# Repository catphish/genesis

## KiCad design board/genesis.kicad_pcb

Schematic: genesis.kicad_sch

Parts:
C1, C2, C24, C39, C40, C42, C49, C51, C53, C59, C60, C98, C99, C100, C109, C110, C111, C112, C113, C114: 10u; C_0805_2012Metric; LCSC C15850
C3, C4, C5, C6, C7, C8, C9, C10, C11, C14, C15, C16, C17, C20, C23, C25, C26, C29, C30, C33, C34, C35, C38, C41, C43, C44, C46, C47, C54, C55, C56, C61, C62, C63, C64, C65, C66, C67, C68, C69, C70, C71, C72, C73, C74, C75, C76, C77, C78, C79, C80, C81, C82, C83, C84, C85, C86, C87, C88, C89, C90, C92, C93, C94, C95, C96, C97, C101, C102, C103, C104, C105, C106, C107, C108: 100n; C_0402_1005Metric; LCSC C307331
C12, C22, C37, C91: 4.7u; C_0805_2012Metric; LCSC C1779
C13, C18, C19, C27, C28, C31, C32, C45, C48, C57, C58: 2.2u; C_0603_1608Metric; LCSC C23630
C21: 33p; C_0402_1005Metric; LCSC C1562
C36: 22p; C_0402_1005Metric; LCSC C1555
C50, C52: 220p; C_0402_1005Metric; LCSC C1530
D1: LED_Dual_AAKK; LED_LiteOn_LTST-C295K_1.6x0.8mm; LCSC C364568
D2, D3: H3V3L10B; D_SOD-882; LCSC C20615781
D4: SMAJ10A; D_SMA; LCSC C134939
F1: nSMD100-16V; Fuse_1206_3216Metric; LCSC C70082
F2, F3: nSMD020-30V; Fuse_1206_3216Metric; LCSC C69680
H1, H2, H3, H4, H5, H6: MountingHole
J1: Conn_02x32_Row_Letter_First; CardEdge_MegaDrive_2x32_P2.54mm_Ears; LCSC C5242019
J2: HDMI_A_1.4; HDMI_A_Molex_208658-1001_Horizontal; LCSC C916313
J3: USB_C_Receptacle_USB2.0_14P; USB_C_Receptacle_Molex_217179-0001; LCSC C3197684
J4: DEBUG_POWER; PinHeader_1x02_P2.54mm_Vertical; LCSC C492401
J5, J6: DE9_Pins_MountingHoles; DSUB-9_Pins_Horizontal_P2.77x2.84mm_EdgePinOffset7.70mm_Hou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; LCSC C426221
JP1: 9V_SELECT; PinHeader_1x03_P2.54mm_Vertical; LCSC C2937625
L1, L2: 2.2u; L_Sunlord_MWSA0503S; LCSC C408408
L3: 1u; L_Sunlord_MWSA0503S; LCSC C408355
Q1, Q2, Q3, Q4, Q5: BSS138; SOT-23; LCSC C52895
Q6: AO3407A; SOT-23; LCSC C15155
R1, R2, R3, R4, R5, R6, R7, R8, R9, R10, R11, R12, R13, R14, R15, R16, R17, R18, R19, R20, R21, R22, R23, R24, R25, R26, R27, R28, R29, R30, R31, R32, R33, R34, R35, R36, R37, R38, R39, R40, R41, R42, R43, R44, R45, R46, R47, R48, R68, R85, R89, R148: 47k; R_0402_1005Metric; LCSC C25792
R49: 1k; R_0402_1005Metric; LCSC C11702
R50, R51, R52, R53, R54, R55: 22; R_0402_1005Metric; LCSC C25092
R56, R57, R58, R59, R60, R61, R62, R63, R64, R65: 270; R_0402_1005Metric; LCSC C25099
R66: 100k; R_0402_1005Metric; LCSC C25741
R67: 150k; R_0402_1005Metric; LCSC C25755
R69: 33k; R_0402_1005Metric; LCSC C25779
R70, R74, R76, R77, R79, R80, R82, R84, R86, R87, R88, R90, R96, R97, R98, R99, R100, R101, R102, R110, R111, R112, R113, R114, R115, R116, R117, R118, R119, R120, R121, R122, R123, R131, R132, R133, R134, R135, R136, R137, R138, R139, R140, R141, R142, R143, R144, R145, R147, R149: 10k; R_0402_1005Metric; LCSC C25744
R71: 53.6k; R_0402_1005Metric; LCSC C53398
R72: 220k; R_0402_1005Metric; LCSC C25767
R73: 8.45k; R_0402_1005Metric; LCSC C270579
R75: 30k; R_0402_1005Metric; LCSC C25776
R78, R81, R83, R91, R92, R93, R94, R95: 4.7k; R_0402_1005Metric; LCSC C25900
R103, R104, R105, R106, R107, R108, R109, R124, R125, R126, R127, R128, R129, R130: 220; R_0805_2012Metric; LCSC C17557
R146: 2.2k; R_0402_1005Metric; LCSC C25879
SW1: SW_RESET; SW_ALPS_SPPH4_Vertical; LCSC C202363
SW2: STM32_RESET; SW_SPST_B3U-1000P; LCSC C231329
SW3: STM32_DFU; SW_SPST_B3U-1000P; LCSC C231329
SW4: SW_POWER; SW_ALPS_SPPH4_Vertical; LCSC C370973
U1, U2, U3, U4, U5, U6, U7, U8, U9, U10, U11, U12, U13, U14, U15, U16, U17, U18, U19, U20, U21, U22, U23, U24, U25, U26, U27, U28, U29, U30, U31, U32, U33, U34, U35, U36, U37, U38, U39, U40, U41, U42, U43, U44, U45, U46, U47, U48, U49, U50, U51, U52, U53, U54, U55, U56, U57, U58, U59, U60, U61, U62, U63, U64, U65, U66, U67, U76, U77, U78, U79: TPD1E05U06DPY; Texas_DPY0002A_0.6x1mm_P0.65mm; LCSC C436349
U68: LFE5U-25F-6BG256C; BGA-256_14.0x14.0mm_Layout16x16_P0.8mm_Ball0.45mm_Pad0.32mm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; LCSC C1550762
U69: W25Q32JVZPIQ; WSON-8-1EP_6x5mm_P1.27mm_EP3.4x4.3mm; LCSC C571260
U70: LP5907MFX-2.5; SOT-23-5; LCSC C165132
U71, U72, U83: SN74ALVC164245DGG; TSSOP-48_6.1x12.5mm_P0.5mm; LCSC C7128
U73: IS61WV25616BLL; TSOP-II-44_10.16x18.41mm_P0.8mm; LCSC C53825
U74, U80, U81: TPS563257DRLR; SOT-563; LCSC C20539656
U75: STM32G431CBTx; LQFP-48_7x7mm_P0.5mm; LCSC C529355
U82: TPD12S016PWR; TSSOP-24_4.4x7.8mm_P0.65mm; LCSC C201665
U84: PCM1808PWR; TSSOP-14_4.4x5mm_P0.65mm; LCSC C55513
U85, U86, U87, U88, U89, U90, U91, U92, U93, U94, U95, U96, U97, U98: SN74LVC1T45DBV; SOT-23-6; LCSC C7843
Y1: 27MHz; Crystal_SMD_SeikoEpson_FA128-4Pin_2.0x1.6mm; LCSC C881727

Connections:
+1V1: C42.1, C92.1, C93.1, C94.1, C95.1, C96.1, C97.1, C98.1, C99.1, C100.1, L3.2, R73.1, U68.G6 (VCC[6]), U68.G7 (VCC[6]), U68.G9 (VCC[6]), U68.L8 (VCC[6]), U68.L9 (VCC[6]), U68.L10 (VCC[6])
+2V5: C19.1, C89.1, C90.1, C91.1, U68.G11 (VCCAUX[2]), U68.L7 (VCCAUX[2]), U70.5 (OUT)
+3V3: C3.1, C4.1, C5.1, C6.1, C7.1, C8.1, C9.1, C10.1, C11.1, C12.1, C13.1, C14.1, C15.1, C16.1, C17.1, C18.1, C21.1, C24.1, C33.1, C40.1, C41.1, C43.1, C44.1, C45.1, C46.1, C61.1, C62.1, C63.1, C64.1, C65.1, C66.1, C67.1, C68.1, C69.1, C70.1, C71.1, C72.1, C73.1, C74.1, C101.1, C102.1, C103.1, C104.1, C105.1, C106.1, C107.1, C108.1, C109.1, C110.1, C111.1, C112.1, C113.1, L1.2, Q1.1 (G), Q2.1 (G), Q3.1 (G), Q4.1 (G), Q5.1 (G), R49.2, R67.1, R78.2, R80.1, R81.2, R83.2, R86.2, R88.2, R90.2, R93.2, R94.2, R95.2, R139.1, R141.1, R143.1, R145.1, R147.1, R149.1, SW3.1, U68.F6 (VCCIO0[2]), U68.F7 (VCCIO0[2]), U68.F10 (VCCIO1[2]), U68.F11 (VCCIO1[2]), U68.H6 (VCCIO7[2]), U68.H7 (VCCIO7[2]), U68.H11 (VCCIO2[2]), U68.J6 (VCCIO6[2]), U68.J7 (VCCIO6[2]), U68.J11 (VCCIO2[2]), U68.K11 (VCCIO3[2]), U68.L6 (VCCIO8), U68.L11 (VCCIO3[2]), U68.P10 (CFG_1), U69.8 (VCC), U70.1 (IN), U70.3 (EN), U71.31 (V_{CC(A)}), U71.42 (V_{CC(A)}), U72.31 (V_{CC(A)}), U72.42 (V_{CC(A)}), U73.11 (VDD), U73.33 (VDD), U75.1 (VBAT), U75.20 (VREF+), U75.21 (VDDA), U75.24 (VDD), U75.36 (VDD), U75.48 (VDD), U81.1 (VIN), U81.5 (EN), U82.24 (VCCA), U83.31 (V_{CC(A)}), U83.42 (V_{CC(A)}), U84.4 (VDD), U85.1 (VCCA), U86.1 (VCCA), U87.1 (VCCA), U88.1 (VCCA), U89.1 (VCCA), U90.1 (VCCA), U91.1 (VCCA), U92.1 (VCCA), U93.1 (VCCA), U94.1 (VCCA), U95.1 (VCCA), U96.1 (VCCA), U97.1 (VCCA), U98.1 (VCCA), Y1.1 (EN), Y1.4 (Vdd)
+5V: C1.1, C2.1, C25.1, C26.1, C27.1, C28.1, C29.1, C30.1, C31.1, C32.1, C35.1, C36.1, C39.1, C47.1, C48.1, C55.1, C56.1, C57.1, C58.1, C75.1, C76.1, C77.1, C78.1, C79.1, C80.1, C81.1, C82.1, C83.1, C84.1, C85.1, C86.1, C87.1, C88.1, C114.1, F1.1, F2.1, F3.1, L2.2, R1.1, R2.1, R3.1, R4.1, R5.1, R6.1, R7.1, R8.1, R9.1, R10.1, R11.1, R12.1, R13.1, R14.1, R15.1, R16.1, R17.1, R18.1, R19.1, R20.1, R21.1, R22.1, R23.1, R24.1, R25.1, R26.1, R27.1, R28.1, R29.1, R30.1, R31.1, R32.1, R33.1, R34.1, R35.1, R36.1, R37.1, R38.1, R39.1, R40.1, R41.1, R42.1, R43.1, R44.1, R45.1, R46.1, R47.1, R48.1, R72.1, R96.1, R97.1, R98.1, R99.1, R100.1, R101.1, R102.1, R117.1, R118.1, R119.1, R120.1, R121.1, R122.1, R123.1, R138.1, R140.1, R142.1, R144.1, R146.1, U71.7 (V_{CC(B)}), U71.18 (V_{CC(B)}), U72.7 (V_{CC(B)}), U72.18 (V_{CC(B)}), U82.11 (VCC5V), U83.7 (V_{CC(B)}), U83.18 (V_{CC(B)}), U84.3 (VCC), U85.6 (VCCB), U86.6 (VCCB), U87.6 (VCCB), U88.6 (VCCB), U89.6 (VCCB), U90.6 (VCCB), U91.6 (VCCB), U92.6 (VCCB), U93.6 (VCCB), U94.6 (VCCB), U95.6 (VCCB), U96.6 (VCCB), U97.6 (VCCB), U98.6 (VCCB)
+9V: J4.2, JP1.1 (A)
/BOOT0: R70.2, SW3.2, U75.45 (PB8)
/STM32_RESET: C20.2, SW2.2, U75.7 (PG10)
BCK: U68.J13 (PR26C/+/RDQ29), U84.8 (BCK)
C1_P1_DATA: U68.B9 (PT47A/+/GR_PCLK1_0), U85.3 (A)
C1_P1_DIR: R110.1, U68.C9 (PT47B/-/GR_PCLK1_1), U85.5 (DIR)
C1_P1_PORT: J5.1, R103.1, U54.1 (I/O)
C1_P2_DATA: U68.D9 (PT49A/+), U86.3 (A)
C1_P2_DIR: R111.1, U68.E9 (PT49B/-), U86.5 (DIR)
C1_P2_PORT: J5.2, R104.1, U55.1 (I/O)
C1_P3_DATA: U68.A9 (PT51A/+), U87.3 (A)
C1_P3_DIR: R112.1, U68.A10 (PT51B/-), U87.5 (DIR)
C1_P3_PORT: J5.3, R105.1, U56.1 (I/O)
C1_P4_DATA: U68.B10 (PT53A/+), U88.3 (A)
C1_P4_DIR: R113.1, U68.C10 (PT53B/-), U88.5 (DIR)
C1_P4_PORT: J5.4, R106.1, U57.1 (I/O)
C1_P5_DATA: U68.D10 (PT56A/+), U89.3 (A)
C1_P5_DIR: R114.1, U68.E10 (PT56B/-), U89.5 (DIR)
C1_P5_PORT: J5.6, R107.1, U58.1 (I/O)
C1_P6_DATA: U68.B11 (PT58A/+), U90.3 (A)
C1_P6_DIR: R115.1, U68.C11 (PT58B/-), U90.5 (DIR)
C1_P6_PORT: J5.7, R108.1, U59.1 (I/O)
C1_P7_DATA: U68.D11 (PT69A/+), U91.3 (A)
C1_P7_DIR: R116.1, U68.E11 (PT69B/-), U91.5 (DIR)
C1_P7_PORT: J5.9, R109.1, U60.1 (I/O)
C2_P1_DATA: U68.A11 (PT71A/+), U92.3 (A)
C2_P1_DIR: R131.1, U68.A12 (PT71B/-), U92.5 (DIR)
C2_P1_PORT: J6.1, R124.1, U61.1 (I/O)
C2_P2_DATA: U68.B12 (PT74A/+), U93.3 (A)
C2_P2_DIR: R132.1, U68.C12 (PT74B/-), U93.5 (DIR)
C2_P2_PORT: J6.2, R125.1, U62.1 (I/O)
C2_P3_DATA: U68.D12 (PT76A/+), U94.3 (A)
C2_P3_DIR: R133.1, U68.E12 (PT76B/-), U94.5 (DIR)
C2_P3_PORT: J6.3, R126.1, U63.1 (I/O)
C2_P4_DATA: U68.B13 (PT78A/+), U95.3 (A)
C2_P4_DIR: R134.1, U68.C13 (PT78B/-), U95.5 (DIR)
C2_P4_PORT: J6.4, R127.1, U64.1 (I/O)
C2_P5_DATA: U68.D13 (PT80A/+), U96.3 (A)
C2_P5_DIR: R135.1, U68.E13 (PT80B/-), U96.5 (DIR)
C2_P5_PORT: J6.6, R128.1, U65.1 (I/O)
C2_P6_DATA: U68.A13 (PT83A/+), U97.3 (A)
C2_P6_DIR: R136.1, U68.A14 (PT83B/-), U97.5 (DIR)
C2_P6_PORT: J6.7, R129.1, U66.1 (I/O)
C2_P7_DATA: U68.B14 (PT85A/+/URC_GPLL1T_IN), U98.3 (A)
C2_P7_DIR: R137.1, U68.A15 (PT85B/-/URC_GPLL1C_IN), U98.5 (DIR)
C2_P7_PORT: J6.9, R130.1, U67.1 (I/O)
CART_ADDR_1: U68.L1 (PL35A/+/PCLKT6_1/HS/LDQ41), U83.47 (1A0)
CART_ADDR_2: U68.L2 (PL35B/-/PCLKC6_1/HS/LDQ41), U83.46 (1A1)
CART_ADDR_3: U68.M1 (PL35C/+/PCLKT6_0/LDQ41), U83.44 (1A2)
CART_ADDR_4: U68.M2 (PL35D/-/PCLKC6_0/LDQ41), U83.43 (1A3)
CART_ADDR_5: U68.K4 (PL38A/+/GR_PCLK6_0/HS/LDQ41), U83.41 (1A4)
CART_ADDR_6: U68.K5 (PL38B/-/HS/LDQ41), U83.40 (1A5)
CART_ADDR_7: U68.L4 (PL38C/+/GR_PCLK6_1/LDQ41), U83.38 (1A6)
CART_ADDR_8: U68.L5 (PL38D/-/LDQ41), U83.37 (1A7)
CART_ADDR_9: U68.N1 (PL41A/+/HS/LDQS41), U83.36 (2A0)
CART_ADDR_10: U68.P2 (PL41B/-/HS/LDQSN41), U83.35 (2A1)
CART_ADDR_11: U68.L3 (PL41C/+/LDQ41), U83.33 (2A2)
CART_ADDR_12: U68.M3 (PL41D/-/LDQ41), U83.32 (2A3)
CART_ADDR_13: U68.P1 (PL44A/+/HS/LDQ41), U83.30 (2A4)
CART_ADDR_14: U68.R1 (PL44B/-/VREF1_6/HS/LDQ41), U83.29 (2A5)
CART_ADDR_15: U68.M4 (PL44C/+/LDQ41), U83.27 (2A6)
CART_ADDR_16: U68.N3 (PL44D/-/LDQ41), U83.26 (2A7)
CART_ADDR_17: U68.N4 (PL59A/+/HS/LDQ65), U71.47 (1A0)
CART_ADDR_18: U68.P3 (PL59B/-/HS/LDQ65), U71.46 (1A1)
CART_ADDR_19: U68.R2 (PL59C/+/LDQ65), U71.44 (1A2)
CART_ADDR_20: U68.T2 (PL59D/-/LDQ65), U71.30 (2A4)
CART_ADDR_21: U68.P4 (PL62A/+/HS/LDQ65), U71.29 (2A5)
CART_ADDR_22: U68.R3 (PL62B/-/HS/LDQ65), U71.27 (2A6)
CART_ADDR_23: U68.R4 (PL62C/+/LDQ65), U71.26 (2A7)
CART_AS: U68.G3 (PL23C/+/VREF1_7/LDQ29), U71.35 (2A1)
CART_ASEL: U68.J5 (PL26D/-/LDQ29), U71.33 (2A2)
CART_CART: Q2.2 (S), R141.2, U68.J1 (PL32A/+/PCLKT7_1/HS/LDQ29)
CART_CAS0: U68.H4 (PL26B/-/HS/LDQ29), U71.43 (1A3)
CART_CAS2: U68.J4 (PL26C/+/LDQ29), U71.40 (1A5)
CART_CE0: U68.H3 (PL23D/-/LDQ29), U71.41 (1A4)
CART_DATA_0: U68.B1 (PL11A/+/ULC_GPLL0T_IN/HS/LDQ17), U72.47 (1A0)
CART_DATA_1: U68.B2 (PL11B/-/ULC_GPLL0C_IN/HS/LDQ17), U72.46 (1A1)
CART_DATA_2: U68.C3 (PL11C/+/LDQ17), U72.44 (1A2)
CART_DATA_3: U68.D3 (PL11D/-/LDQ17), U72.43 (1A3)
CART_DATA_4: U68.C1 (PL14A/+/HS/LDQ17), U72.41 (1A4)
CART_DATA_5: U68.C2 (PL14B/-/HS/LDQ17), U72.40 (1A5)
CART_DATA_6: U68.E3 (PL14C/+/LDQ17), U72.38 (1A6)
CART_DATA_7: U68.F3 (PL14D/-/LDQ17), U72.37 (1A7)
CART_DATA_8: U68.D1 (PL17A/+/HS/LDQS17), U72.36 (2A0)
CART_DATA_9: U68.E2 (PL17B/-/HS/LDQSN17), U72.35 (2A1)
CART_DATA_10: U68.F4 (PL17C/+/LDQ17), U72.33 (2A2)
CART_DATA_11: U68.F5 (PL17D/-/LDQ17), U72.32 (2A3)
CART_DATA_12: U68.G5 (PL20A/+/HS/LDQ17), U72.30 (2A4)
CART_DATA_13: U68.G4 (PL20B/-/HS/LDQ17), U72.29 (2A5)
CART_DATA_14: U68.F2 (PL20C/+/LDQ17), U72.27 (2A6)
CART_DATA_15: U68.E1 (PL20D/-/LDQ17), U72.26 (2A7)
CART_DATA_DIR: R87.1, U68.K2 (PL32D/-/PCLKC7_0/LDQ29), U72.1 (1DIR), U72.24 (2DIR)
CART_DATA_OE: R77.1, U68.K1 (PL32C/+/PCLKT7_0/LDQ29), U72.25 (2~OE), U72.48 (1~OE)
CART_DIR: R84.1, U68.K14 (PR29D/-/RDQ29), U71.1 (1DIR), U83.1 (1DIR), U83.24 (2DIR)
CART_DTACK: Q5.2 (S), R147.2, U68.K3 (PL29D/-/LDQ29)
CART_LWR: U68.H2 (PL29B/-/HS/LDQSN29), U71.37 (1A7)
CART_M3: Q1.2 (S), R139.2, U68.J2 (PL32B/-/PCLKC7_1/HS/LDQ29)
CART_MRES: Q4.2 (S), R145.2, U68.K16 (PR32C/+/PCLKT2_0/RDQ29)
CART_OE: R79.1, U68.J16 (PR32A/+/PCLKT2_1/HS/RDQ29), U71.25 (2~OE), U71.48 (1~OE), U83.25 (2~OE), U83.48 (1~OE)
CART_SLOT_ADDR_1: J1.a17, R17.2, U32.1 (I/O), U83.2 (1B0)
CART_SLOT_ADDR_2: J1.a15, R18.2, U30.1 (I/O), U83.3 (1B1)
CART_SLOT_ADDR_3: J1.a13, R19.2, U28.1 (I/O), U83.5 (1B2)
CART_SLOT_ADDR_4: J1.a11, R20.2, U27.1 (I/O), U83.6 (1B3)
CART_SLOT_ADDR_5: J1.a9, R21.2, U33.1 (I/O), U83.8 (1B4)
CART_SLOT_ADDR_6: J1.a7, R22.2, U23.1 (I/O), U83.9 (1B5)
CART_SLOT_ADDR_7: J1.a5, R23.2, U21.1 (I/O), U83.11 (1B6)
CART_SLOT_ADDR_8: J1.a3, R24.2, U19.1 (I/O), U83.12 (1B7)
CART_SLOT_ADDR_9: J1.b4, R25.2, U18.1 (I/O), U83.13 (2B0)
CART_SLOT_ADDR_10: J1.b5, R26.2, U6.1 (I/O), U83.14 (2B1)
CART_SLOT_ADDR_11: J1.a4, R27.2, U20.1 (I/O), U83.16 (2B2)
CART_SLOT_ADDR_12: J1.a6, R28.2, U22.1 (I/O), U83.17 (2B3)
CART_SLOT_ADDR_13: J1.a8, R29.2, U24.1 (I/O), U83.19 (2B4)
CART_SLOT_ADDR_14: J1.a10, R30.2, U25.1 (I/O), U83.20 (2B5)
CART_SLOT_ADDR_15: J1.a12, R31.2, U26.1 (I/O), U83.22 (2B6)
CART_SLOT_ADDR_16: J1.a14, R32.2, U29.1 (I/O), U83.23 (2B7)
CART_SLOT_ADDR_17: J1.a16, R33.2, U31.1 (I/O), U71.2 (1B0)
CART_SLOT_ADDR_18: J1.b6, R34.2, U17.1 (I/O), U71.3 (1B1)
CART_SLOT_ADDR_19: J1.b7, R35.2, U16.1 (I/O), U71.5 (1B2)
CART_SLOT_ADDR_20: J1.b8, R36.2, U53.1 (I/O), U71.19 (2B4)
CART_SLOT_ADDR_21: J1.b9, R37.2, U52.1 (I/O), U71.20 (2B5)
CART_SLOT_ADDR_22: J1.b10, R38.2, U51.1 (I/O), U71.22 (2B6)
CART_SLOT_ADDR_23: J1.b11, R39.2, U50.1 (I/O), U71.23 (2B7)
CART_SLOT_AS: J1.b18, R46.2, U2.1 (I/O), U71.14 (2B1)
CART_SLOT_ASEL: J1.b26, R47.2, U9.1 (I/O), U71.16 (2B2)
CART_SLOT_CART: J1.b32, Q2.3 (D), R140.2, U15.1 (I/O)
CART_SLOT_CAS0: J1.b16, R40.2, U7.1 (I/O), U71.6 (1B3)
CART_SLOT_CAS2: J1.b21, R42.2, U8.1 (I/O), U71.9 (1B5)
CART_SLOT_CE0: J1.b17, R41.2, U3.1 (I/O), U71.8 (1B4)
CART_SLOT_DATA_0: J1.a20, R1.2, U39.1 (I/O), U72.2 (1B0)
CART_SLOT_DATA_1: J1.a23, R2.2, U42.1 (I/O), U72.3 (1B1)
CART_SLOT_DATA_2: J1.a26, R3.2, U45.1 (I/O), U72.5 (1B2)
CART_SLOT_DATA_3: J1.a29, R4.2, U48.1 (I/O), U72.6 (1B3)
CART_SLOT_DATA_4: J1.a28, R5.2, U47.1 (I/O), U72.8 (1B4)
CART_SLOT_DATA_5: J1.a25, R6.2, U44.1 (I/O), U72.9 (1B5)
CART_SLOT_DATA_6: J1.a22, R7.2, U41.1 (I/O), U72.11 (1B6)
CART_SLOT_DATA_7: J1.a19, R8.2, U38.1 (I/O), U72.12 (1B7)
CART_SLOT_DATA_8: J1.a21, R9.2, U40.1 (I/O), U72.13 (2B0)
CART_SLOT_DATA_9: J1.a24, R10.2, U43.1 (I/O), U72.14 (2B1)
CART_SLOT_DATA_10: J1.a27, R11.2, U46.1 (I/O), U72.16 (2B2)
CART_SLOT_DATA_11: J1.a30, R12.2, U49.1 (I/O), U72.17 (2B3)
CART_SLOT_DATA_12: J1.b25, R13.2, U34.1 (I/O), U72.19 (2B4)
CART_SLOT_DATA_13: J1.b24, R14.2, U35.1 (I/O), U72.20 (2B5)
CART_SLOT_DATA_14: J1.b23, R15.2, U36.1 (I/O), U72.22 (2B6)
CART_SLOT_DATA_15: J1.b22, R16.2, U37.1 (I/O), U72.23 (2B7)
CART_SLOT_DTACK: J1.b20, Q5.3 (D), R146.2, U5.1 (I/O)
CART_SLOT_EDCLK: J1.b15
CART_SLOT_HSYNC: J1.b14
CART_SLOT_LWR: J1.b28, R44.2, U11.1 (I/O), U71.12 (1B7)
CART_SLOT_M3: J1.b30, Q1.3 (D), R138.2, U13.1 (I/O)
CART_SLOT_MRES: J1.b2, Q4.3 (D), R144.2, U1.1 (I/O)
CART_SLOT_SL1: C49.1, D2.2 (A2), J1.b1, R85.2
CART_SLOT_SR1: C51.1, D3.2 (A2), J1.b3, R89.2
CART_SLOT_TIME: J1.b31, R48.2, U14.1 (I/O), U71.17 (2B3)
CART_SLOT_UWR: J1.b29, R45.2, U12.1 (I/O), U71.13 (2B0)
CART_SLOT_VCLK: J1.b19, R43.2, U4.1 (I/O), U71.11 (1B6)
CART_SLOT_VRES: J1.b27, Q3.3 (D), R142.2, U10.1 (I/O)
CART_SLOT_VSYNC: J1.b13
CART_SLOT_YS: J1.b12
CART_TIME: U68.H5 (PL26A/+/HS/LDQ29), U71.32 (2A3)
CART_UWR: U68.G1 (PL29A/+/GR_PCLK7_1/HS/LDQS29), U71.36 (2A0)
CART_VA_HI_DIR: R82.1, U68.J15 (PR32B/-/PCLKC2_1/HS/RDQ29), U71.24 (2DIR)
CART_VCLK: U68.J3 (PL29C/+/GR_PCLK7_0/LDQ29), U71.38 (1A6)
CART_VRES: Q3.2 (S), R143.2, U68.K15 (PR32D/-/PCLKC2_0/RDQ29)
CC1: C50.1, J3.A5 (CC1), U75.31 (PA9), U75.43 (PB6), U78.1 (I/O)
CC2: C52.1, J3.B5 (CC2), U75.32 (PA10), U75.41 (PB4), U79.1 (I/O)
CLK_MASTER: U68.E8 (PT42A/+/PCLKT1_1), Y1.3 (OUT)
D+: J3.A6 (D+), J3.B6 (D+), U75.34 (PA12), U76.1 (I/O)
D-: J3.A7 (D-), J3.B7 (D-), U75.33 (PA11), U77.1 (I/O)
DONE: R81.1, U68.P9 (DONE), U75.10 (PA2)
DOUT: U68.H12 (PR26A/+/HS/RDQ29), U84.9 (DOUT)
FLASH_CLK: R49.1, R50.1, U69.6 (CLK)
FLASH_CS_N: R55.1, R86.1, U69.1 (~CS)
FLASH_D0: R54.1, U69.5 (DI/IO_{0})
FLASH_D1: R53.1, U69.2 (DO/IO_{1})
FLASH_D2: R52.1, R88.1, U69.3 (~WP/IO_{2})
FLASH_D3: R51.1, R90.1, U69.7 (~HOLD/~RESET/IO_{3})
GND: C1.2, C2.2, C3.2, C4.2, C5.2, C6.2, C7.2, C8.2, C9.2, C10.2, C11.2, C12.2, C13.2, C14.2, C15.2, C16.2, C17.2, C18.2, C19.2, C20.1, C22.2, C23.2, C24.2, C25.2, C26.2, C27.2, C28.2, C29.2, C30.2, C31.2, C32.2, C33.2, C34.2, C35.2, C37.2, C38.2, C39.2, C40.2, C41.2, C42.2, C43.2, C44.2, C45.2, C46.2, C47.2, C48.2, C50.2, C52.2, C53.2, C54.2, C55.2, C56.2, C57.2, C58.2, C59.1, C60.1, C61.2, C62.2, C63.2, C64.2, C65.2, C66.2, C67.2, C68.2, C69.2, C70.2, C71.2, C72.2, C73.2, C74.2, C75.2, C76.2, C77.2, C78.2, C79.2, C80.2, C81.2, C82.2, C83.2, C84.2, C85.2, C86.2, C87.2, C88.2, C89.2, C90.2, C91.2, C92.2, C93.2, C94.2, C95.2, C96.2, C97.2, C98.2, C99.2, C100.2, C101.2, C102.2, C103.2, C104.2, C105.2, C106.2, C107.2, C108.2, C109.2, C110.2, C111.2, C112.2, C113.2, C114.2, D1.3 (K1), D1.4 (K2), D2.1 (A1), D3.1 (A1), D4.2 (A2), J1.a1, J1.a18, J1.a32, J2.2 (D2S), J2.5 (D1S), J2.8 (D0S), J2.11 (CKS), J2.17 (GND), J2.SH, J3.A1 (GND), J3.A12 (GND), J3.B1 (GND), J3.B12 (GND), J3.SH (SHIELD), J4.1, J5.8, J5.SH (PAD), J6.8, J6.SH (PAD), R68.2, R69.2, R70.1, R74.2, R75.2, R76.2, R77.2, R79.2, R82.2, R84.2, R85.1, R87.2, R89.1, R91.2, R92.2, R110.2, R111.2, R112.2, R113.2, R114.2, R115.2, R116.2, R131.2, R132.2, R133.2, R134.2, R135.2, R136.2, R137.2, SW1.1, SW2.1, SW4.1 (A), U1.2 (GND), U2.2 (GND), U3.2 (GND), U4.2 (GND), U5.2 (GND), U6.2 (GND), U7.2 (GND), U8.2 (GND), U9.2 (GND), U10.2 (GND), U11.2 (GND), U12.2 (GND), U13.2 (GND), U14.2 (GND), U15.2 (GND), U16.2 (GND), U17.2 (GND), U18.2 (GND), U19.2 (GND), U20.2 (GND), U21.2 (GND), U22.2 (GND), U23.2 (GND), U24.2 (GND), U25.2 (GND), U26.2 (GND), U27.2 (GND), U28.2 (GND), U29.2 (GND), U30.2 (GND), U31.2 (GND), U32.2 (GND), U33.2 (GND), U34.2 (GND), U35.2 (GND), U36.2 (GND), U37.2 (GND), U38.2 (GND), U39.2 (GND), U40.2 (GND), U41.2 (GND), U42.2 (GND), U43.2 (GND), U44.2 (GND), U45.2 (GND), U46.2 (GND), U47.2 (GND), U48.2 (GND), U49.2 (GND), U50.2 (GND), U51.2 (GND), U52.2 (GND), U53.2 (GND), U54.2 (GND), U55.2 (GND), U56.2 (GND), U57.2 (GND), U58.2 (GND), U59.2 (GND), U60.2 (GND), U61.2 (GND), U62.2 (GND), U63.2 (GND), U64.2 (GND), U65.2 (GND), U66.2 (GND), U67.2 (GND), U68.A1 (GND[27]), U68.A16 (GND[27]), U68.D2 (GND[27]), U68.D15 (GND[27]), U68.F8 (GND[27]), U68.F9 (GND[27]), U68.G8 (GND[27]), U68.G10 (GND[27]), U68.H1 (GND[27]), U68.H8 (GND[27]), U68.H9 (GND[27]), U68.H10 (GND[27]), U68.H16 (GND[27]), U68.J8 (GND[27]), U68.J9 (GND[27]), U68.J10 (GND[27]), U68.K6 (GND[27]), U68.K7 (GND[27]), U68.K8 (GND[27]), U68.K9 (GND[27]), U68.K10 (GND[27]), U68.N2 (GND[27]), U68.N10 (CFG_0), U68.N15 (GND[27]), U68.R10 (CFG_2), U68.T1 (GND[27]), U68.T5 (GND[27]), U68.T12 (GND[27]), U68.T16 (GND[27]), U69.4 (GND), U69.9 (EP), U70.2 (GND), U71.4 (GND), U71.10 (GND), U71.15 (GND), U71.21 (GND), U71.28 (GND), U71.34 (GND), U71.39 (GND), U71.45 (GND), U72.4 (GND), U72.10 (GND), U72.15 (GND), U72.21 (GND), U72.28 (GND), U72.34 (GND), U72.39 (GND), U72.45 (GND), U73.12 (GND), U73.34 (GND), U74.3 (GND), U75.19 (VSSA), U75.23 (VSS), U75.35 (VSS), U75.47 (VSS), U76.2 (GND), U77.2 (GND), U78.2 (GND), U79.2 (GND), U80.3 (GND), U81.3 (GND), U82.6 (GND), U82.14 (GND), U82.19 (GND), U83.4 (GND), U83.10 (GND), U83.15 (GND), U83.21 (GND), U83.28 (GND), U83.34 (GND), U83.39 (GND), U83.45 (GND), U84.2 (AGND), U84.5 (DGND), U84.10 (MD0), U84.11 (MD1), U84.12 (FMT), U85.2 (GND), U86.2 (GND), U87.2 (GND), U88.2 (GND), U89.2 (GND), U90.2 (GND), U91.2 (GND), U92.2 (GND), U93.2 (GND), U94.2 (GND), U95.2 (GND), U96.2 (GND), U97.2 (GND), U98.2 (GND), Y1.2 (GND)
HDMI_5V: C34.1, J2.18 (+5V), U82.13 (5V_OUT)
HDMI_CEC: U68.D5 (PT13B/-), U82.1 (CEC_A)
HDMI_CLK+: R64.1, U68.C4 (PT11A/+), U82.16 (CLK+)
HDMI_CLK-: R65.1, U68.B4 (PT11B/-), U82.15 (CLK-)
HDMI_CT_HPD: U68.A6 (PT18B/-), U82.12 (CT_HPD)
HDMI_D0+: R62.1, U68.A2 (PT4A/+/ULC_GPLL1T_IN), U82.18 (D0+)
HDMI_D0-: R63.1, U68.B3 (PT4B/-/ULC_GPLL1C_IN), U82.17 (D0-)
HDMI_D1+: R59.1, U68.A3 (PT6A/+), U82.21 (D1+)
HDMI_D1-: R60.1, U68.A4 (PT6B/-), U82.20 (D1-)
HDMI_D2+: R56.1, U68.E4 (PT9A/+), U82.23 (D2+)
HDMI_D2-: R57.1, U68.D4 (PT9B/-), U82.22 (D2-)
HDMI_HPD: U68.A5 (PT18A/+), U82.4 (HPD_A)
HDMI_LS_OE: U68.E6 (PT20A/+), U82.5 (LS_OE)
HDMI_PORT_CEC: J2.13 (CEC), U82.7 (CEC_B)
HDMI_PORT_HPD: J2.19 (HPD/HEAC-), U82.10 (HPD_B)
HDMI_PORT_SCL: J2.15 (SCL), U82.8 (SCL_B)
HDMI_PORT_SDA: J2.16 (SDA), U82.9 (SDA_B)
HDMI_SCL: U68.C5 (PT15A/+), U82.2 (SCL_A)
HDMI_SDA: U68.B5 (PT15B/-), U82.3 (SDA_A)
INITN: R83.1, U68.T9 (INITN), U75.9 (PA1)
LED_G: R61.2, U68.B7 (PT36B/-/PCLKC0_1)
LED_R: R58.2, U68.A7 (PT38A/+/PCLKT0_0)
LRCK: U68.H13 (PR26B/-/HS/RDQ29), U84.7 (LRCK)
unnamed: C59.2, F2.2, J5.5
unnamed: C60.2, F3.2, J6.5
unnamed: D1.1 (A1), R61.1
unnamed: D1.2 (A2), R58.1
unnamed: F1.2, J1.a2, J1.a31
unnamed: J2.10 (CK+), R64.2
unnamed: J2.12 (CK-), R65.2
unnamed: J2.7 (D0+), R62.2
unnamed: J2.9 (D0-), R63.2
unnamed: J2.4 (D1+), R59.2
unnamed: J2.6 (D1-), R60.2
unnamed: J2.1 (D2+), R56.2
unnamed: J2.3 (D2-), R57.2
unnamed: Q6.1 (G), R148.1, SW4.2 (B)
unnamed: R50.2, U68.N9 (CCLK/MCLK/SCK)
unnamed: R51.2, U68.N7 (PB9A/+/D3/IO3)
unnamed: R52.2, U68.M7 (PB9B/-/D2/IO2)
unnamed: R53.2, U68.T7 (PB11A/+/D1/MISO/IO1)
unnamed: R54.2, U68.T8 (PB11B/-/D0/MOSI/IO0)
unnamed: R55.2, U68.N8 (PB15A/+/HOLDN/DI/BUSY/CSSPIN/CEN)
unnamed: R66.2, R68.1, U74.5 (EN)
unnamed: C21.2, R67.2, R69.1, U74.6 (FB)
unnamed: L1.1, U74.2 (SW)
unnamed: R71.2, R74.1, U80.5 (EN)
unnamed: C36.2, R72.2, R75.1, U80.6 (FB)
unnamed: L2.1, U80.2 (SW)
unnamed: R73.2, R76.1, U81.6 (FB)
unnamed: L3.1, U81.2 (SW)
unnamed: C49.2, U84.13 (VINL)
unnamed: C51.2, U84.14 (VINR)
unnamed: C53.1, C54.1, U84.1 (VREF)
unnamed: R96.2, R103.2, U85.4 (B)
unnamed: R97.2, R104.2, U86.4 (B)
unnamed: R98.2, R105.2, U87.4 (B)
unnamed: R99.2, R106.2, U88.4 (B)
unnamed: R100.2, R107.2, U89.4 (B)
unnamed: R101.2, R108.2, U90.4 (B)
unnamed: R102.2, R109.2, U91.4 (B)
unnamed: R117.2, R124.2, U92.4 (B)
unnamed: R118.2, R125.2, U93.4 (B)
unnamed: R119.2, R126.2, U94.4 (B)
unnamed: R120.2, R127.2, U95.4 (B)
unnamed: R121.2, R128.2, U96.4 (B)
unnamed: R122.2, R129.2, U97.4 (B)
unnamed: R123.2, R130.2, U98.4 (B)
PG_5V: R80.2, U68.A8 (PT38B/-/PCLKC0_0), U80.4 (PG)
POWER_IN: D4.1 (A1), JP1.2 (C), Q6.2 (S), R148.2
PROGRAMN: R78.1, U68.R9 (PROGRAMN), U75.11 (PA3)
RESET: R149.2, SW1.2, U68.D7 (PT33B/-/GR_PCLK0_0)
SCKI: R91.1, U68.J12 (PR26D/-/RDQ29), U84.6 (SCKI)
SRAM_ADDR_0: U68.B16 (PR11A/+/URC_GPLL0T_IN/HS/RDQ17), U73.1 (A0)
SRAM_ADDR_1: U68.B15 (PR11B/-/URC_GPLL0C_IN/HS/RDQ17), U73.2 (A1)
SRAM_ADDR_2: U68.C14 (PR11C/+/RDQ17), U73.3 (A2)
SRAM_ADDR_3: U68.D14 (PR11D/-/RDQ17), U73.4 (A3)
SRAM_ADDR_4: U68.C16 (PR14A/+/HS/RDQ17), U73.5 (A4)
SRAM_ADDR_5: U68.C15 (PR14B/-/HS/RDQ17), U73.18 (A5)
SRAM_ADDR_6: U68.E14 (PR14C/+/RDQ17), U73.19 (A6)
SRAM_ADDR_7: U68.F14 (PR14D/-/RDQ17), U73.20 (A7)
SRAM_ADDR_8: U68.D16 (PR17A/+/HS/RDQS17), U73.21 (A8)
SRAM_ADDR_9: U68.E15 (PR17B/-/HS/RDQSN17), U73.22 (A9)
SRAM_ADDR_10: U68.F13 (PR17C/+/RDQ17), U73.23 (A10)
SRAM_ADDR_11: U68.F12 (PR17D/-/RDQ17), U73.24 (A11)
SRAM_ADDR_12: U68.G12 (PR20A/+/HS/RDQ17), U73.25 (A12)
SRAM_ADDR_13: U68.G13 (PR20B/-/HS/RDQ17), U73.26 (A13)
SRAM_ADDR_14: U68.F15 (PR20C/+/RDQ17), U73.27 (A14)
SRAM_ADDR_15: U68.E16 (PR20D/-/RDQ17), U73.42 (A15)
SRAM_ADDR_16: U68.F16 (PR23A/+/HS/RDQ29), U73.43 (A16)
SRAM_ADDR_17: U68.G15 (PR23B/-/HS/RDQ29), U73.44 (A17)
SRAM_CE: U68.R14 (PR62B/-/HS/RDQ65), U73.6 (~CE)
SRAM_DATA_0: U68.K13 (PR38A/+/GR_PCLK3_0/HS/RDQ41), U73.7 (D0)
SRAM_DATA_1: U68.K12 (PR38B/-/HS/RDQ41), U73.8 (D1)
SRAM_DATA_2: U68.L13 (PR38C/+/GR_PCLK3_1/RDQ41), U73.9 (D2)
SRAM_DATA_3: U68.L12 (PR38D/-/RDQ41), U73.10 (D3)
SRAM_DATA_4: U68.N16 (PR41A/+/HS/RDQS41), U73.13 (D4)
SRAM_DATA_5: U68.P15 (PR41B/-/HS/RDQSN41), U73.14 (D5)
SRAM_DATA_6: U68.L14 (PR41C/+/RDQ41), U73.15 (D6)
SRAM_DATA_7: U68.M14 (PR41D/-/RDQ41), U73.16 (D7)
SRAM_DATA_8: U68.P16 (PR44A/+/HS/RDQ41), U73.29 (D8)
SRAM_DATA_9: U68.R16 (PR44B/-/VREF1_3/HS/RDQ41), U73.30 (D9)
SRAM_DATA_10: U68.M13 (PR44C/+/RDQ41), U73.31 (D10)
SRAM_DATA_11: U68.N14 (PR44D/-/RDQ41), U73.32 (D11)
SRAM_DATA_12: U68.N13 (PR59A/+/HS/RDQ65), U73.35 (D12)
SRAM_DATA_13: U68.P14 (PR59B/-/HS/RDQ65), U73.36 (D13)
SRAM_DATA_14: U68.R15 (PR59C/+/RDQ65), U73.37 (D14)
SRAM_DATA_15: U68.T15 (PR59D/-/RDQ65), U73.38 (D15)
SRAM_LB: U68.T14 (PR62D/-/RDQ65), U73.39 (~LB)
SRAM_OE: U68.T13 (PR65B/-/HS/RDQSN65), U73.41 (~OE)
SRAM_UB: U68.R12 (PR65A/+/HS/RDQS65), U73.40 (~UB)
SRAM_WE: U68.R13 (PR62C/+/RDQ65), U73.17 (~WE)
TCK: R92.1, U68.T10 (TCK), U75.13 (PA5)
TDI: R93.1, U68.R11 (TDI), U75.15 (PA7)
TDO: R94.1, U68.M10 (TDO), U75.14 (PA6)
TMS: R95.1, U68.T11 (TMS), U75.12 (PA4)
VBUS: J3.A4 (VBUS), J3.A9 (VBUS), J3.B4 (VBUS), J3.B9 (VBUS), JP1.3 (B)
VCC: C22.1, C23.1, C37.1, C38.1, Q6.3 (D), R66.1, R71.1, U74.1 (VIN), U80.1 (VIN)

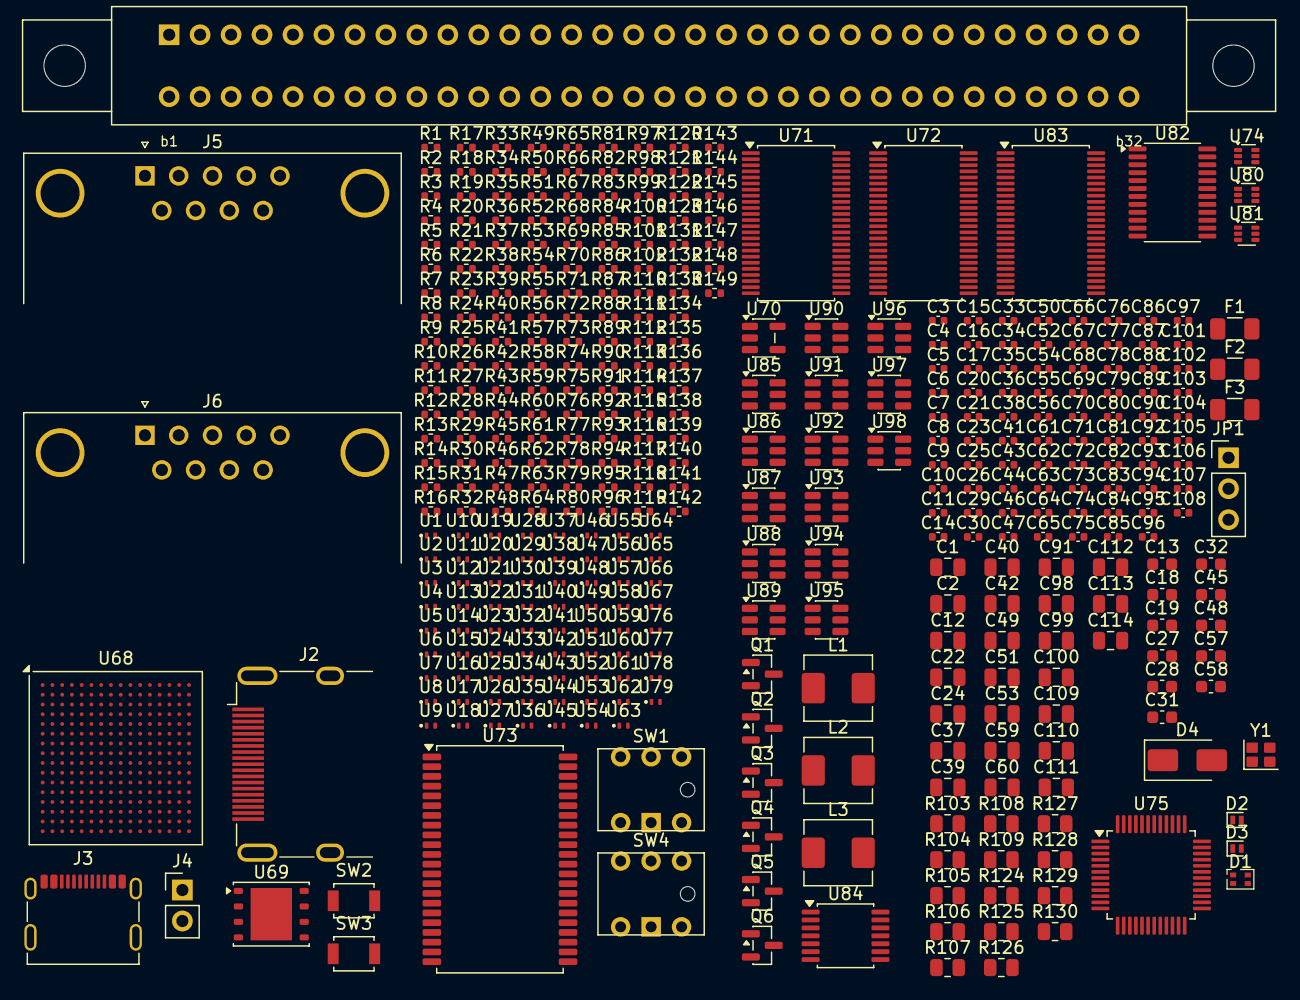
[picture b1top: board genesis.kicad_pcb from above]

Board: 2 copper layers, 389 parts (0 on the bottom side), 295 nets, no tracks yet.

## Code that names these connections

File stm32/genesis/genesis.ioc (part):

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Mcu.Name=STM32G431C(6-8-B)Tx
Mcu.Package=LQFP48
Mcu.UserName=STM32G431CBTx
PA1.Signal=GPIO_Input
PA10.Mode=EnableDeadBattery
PA10.Signal=UCPD1_DBCC2
PA11.Mode=Device
PA11.Signal=USB_DM
PA12.Mode=Device
PA12.Signal=USB_DP
PA5.Mode=Full_Duplex_Master
PA5.Signal=SPI1_SCK
PA6.Mode=Full_Duplex_Master
PA6.Signal=SPI1_MISO
PA7.Mode=Full_Duplex_Master
PA7.Signal=SPI1_MOSI
PA9.Mode=EnableDeadBattery
PA9.Signal=UCPD1_DBCC1
PB0.Signal=GPIO_Output
PB4.Mode=Sink_AllSignals
PB4.Signal=UCPD1_CC2
PB6.Mode=Sink_AllSignals
PB6.Signal=UCPD1_CC1
RCC.HSE_VALUE=8000000
RCC.SYSCLKFreq_VALUE=16000000
board=custom
